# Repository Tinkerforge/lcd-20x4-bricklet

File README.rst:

LCD 20x4 Bricklet
=================

This repository contains the firmware source code and the hardware design
files. The documentation generator configs can be found at
https://github.com/Tinkerforge/generators

Repository Content
------------------

software/:
 * examples/: Examples for all supported languages
 * build/: Compiled files
 * src/: Source code of firmware
 * Makefile: Makefile to build project

hardware/:
 * Contains KiCad project files and additionally schematics as PDF

datasheets/:
 * Contains datasheets for sensors and complex ICs that are used

Hardware
--------

The hardware is designed with the open source EDA Suite KiCad
(http://www.kicad.org). Before you are able to open the files,
you have to install the Tinkerforge kicad-libraries
(https://github.com/Tinkerforge/kicad-libraries). You can either clone
them directly in hardware/ or clone them in a separate folder and
symlink them into hardware/
(ln -s kicad_path/kicad-libraries project_path/hardware). After that you
can open the .pro file in hardware/ with KiCad and from there view and
modify the schematics and the PCB layout.

Software
--------

If you want to do your own Brick/Bricklet firmware development we highly
recommend that you use our build environment setup script and read the
tutorial (https://www.tinkerforge.com/en/doc/Tutorials/Tutorial_Build_Environment/Tutorial.html).

To compile the C code we recommend you to install the newest GNU Arm Embedded
Toolchain (https://launchpad.net/gcc-arm-embedded/+download).
You also need to install bricklib (https://github.com/Tinkerforge/bricklib)
and brickletlib (https://github.com/Tinkerforge/brickletlib).

You can either clone it directly in software/src/ or clone it in a
separate folder and symlink it into software/src/
(ln -s bricklib_path/bricklib project_path/software/src/ and
ln -s brickletlib_path/brickletlib project_path/software/src/).
Finally make sure to have CMake installed
(http://www.cmake.org/cmake/resources/software.html).

After that you can build the firmware by invoking make in software/.
The firmware (.bin) can then be found in software/build/ and uploaded
with brickv (click button "Flashing" on start screen).

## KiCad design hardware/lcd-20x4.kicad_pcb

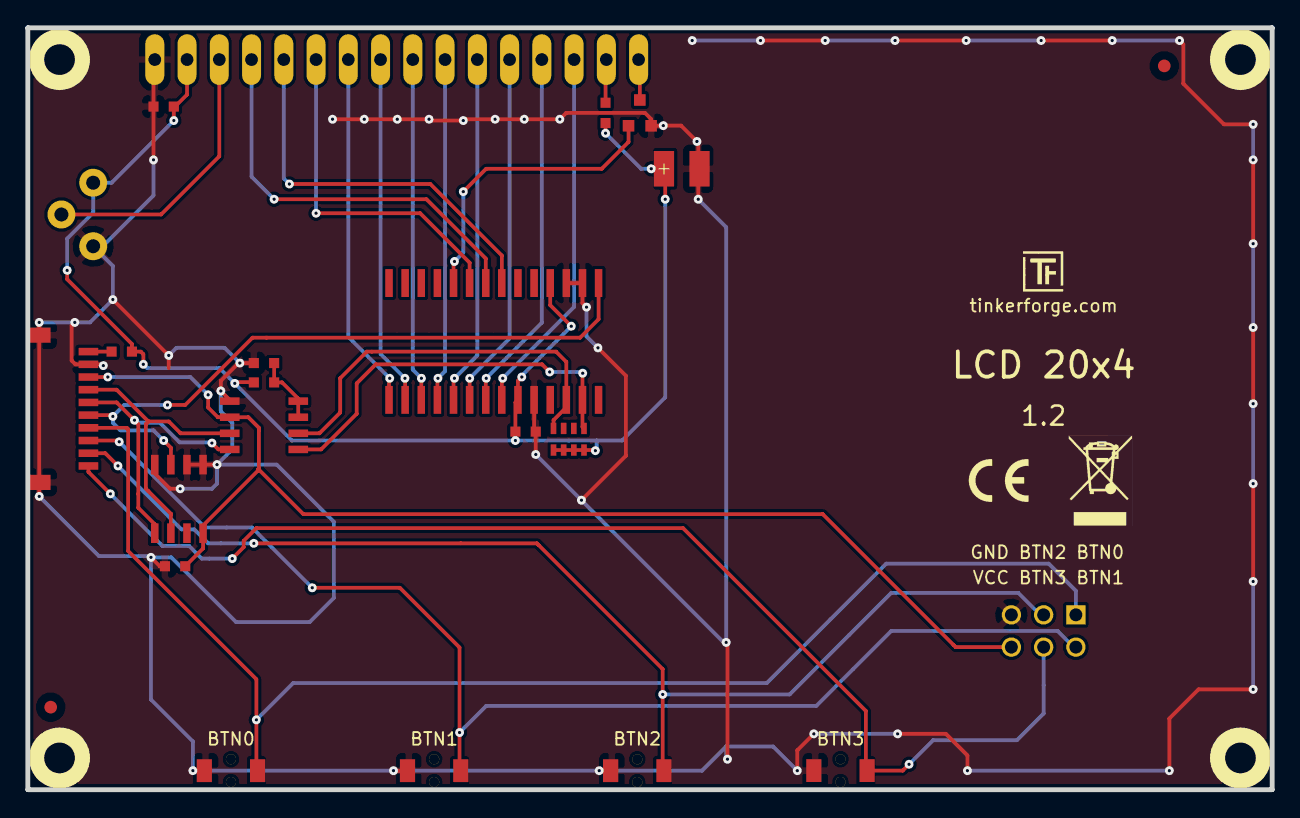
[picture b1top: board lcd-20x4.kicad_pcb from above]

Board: 2 copper layers, 98.0 x 60.0 mm, 30 parts (0 on the bottom side), 29 nets.

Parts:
C1, C2, C3, C5: 100nF; C0603
C4: 100µF/6.3V; 3528-21
FB1: FB; C0603
Fiducial_Mark: VAL**; Fiducial_Mark
Fiducial_Mark#2: VAL**; Fiducial_Mark
P1: CON-SENSOR
P2: BTN-HEADER; pin_array_3x2
Q1: 2N7002; SOT23GDS
R1: 200k; R0603
R2: 10; R0603
RP1: 4.7k; 0603X4
RV1: 10k; POT_36W
Ref**: Val**; Logo_31x31
SW1, SW2, SW3, SW4: SW_PUSH; TACT-SWITCH
U1: M24C64; SOIC8
U2: MCP23017; SOIC28
U3: PCA9306D; SOIC8
U4: LCD-20X4; LCD-20x4
U5, U6, U7, U8: DRILL; DRILL_NP
VAL: WEEE_7mm_back
VAL#2: CE_5mm

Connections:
+5V: C2.1, C4.1, C5.2, FB1.2, R1.1, R2.2, RP1.1, RP1.2, RP1.3, RP1.4, RV1.1, U2.9, U2.18, U4.2
BTN1: P1.7, P2.1, SW1.1
BTN2: P1.8, P2.2, SW2.1
BTN3: P1.9, P2.3, SW3.1
BTN4: P1.10, P2.4, SW4.1
DB0: U2.1, U4.7
DB1: U2.2, U4.8
DB2: U2.3, U4.9
DB3: U2.4, U4.10
DB4: U2.5, U4.11
DB5: U2.6, U4.12
DB6: U2.7, U4.13
DB7: U2.8, U4.14
EN: U2.23, U4.6
GND: C1.1, C2.2, C3.2, C4.2, C5.1, P1.2, P1.EP, P2.5, Q1.S, RV1.3, SW1.2, SW2.2, SW3.2, SW4.2, U1.1, U1.2, U1.4, U2.10, U2.16, U2.17, U3.1, U4.1
unnamed: C3.1, R1.2, U3.7, U3.8
unnamed: FB1.1, P1.1
unnamed: Q1.D, U4.16
unnamed: R2.1, U4.15
unnamed: RV1.2, U4.3
RS: U2.22, U4.4
RW: U2.21, U4.5
SCL: P1.4, U1.6, U3.3
SCL2: RP1.8, U2.12, U3.6
SDA: P1.5, U1.5, U3.4
SDA2: RP1.5, U2.13, U3.5
SEL: P1.6, U1.3, U2.15
SW-BACK: Q1.G, U2.24
VCC: C1.2, P1.3, P2.6, U1.8, U3.2

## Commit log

2011-08-25 initial hardware source commit
2011-08-25 add project description
2011-09-13 add java bindings and examples
2011-09-14 limit line length of java examples to 100 characters
2011-09-23 Add C# examples and bindings
2011-10-05 Remove Bindings and IP Connection (these are generated and they change too often) and rename bindings to examples
2011-10-05 add tinkerforge package to python imports
2011-10-06 remove faulty gcc commandline invocation
2011-10-06 add firmware version and name
2011-11-20 use clear display wait time, we experienced problems without it
2012-02-14 add compatability for different tick types
2012-02-15 Add changelog
2012-02-15 Move software changelog to software folder
2012-04-25 Unify capitalization of "IP connection" in examples
2012-05-09 Add PHP examples
2012-05-13 Add standard LCD charset PDF
2012-05-14 java: Remove unnecessary new String(...) calls
2012-05-21 Add Unicode examples
2012-05-21 Shorten some long lines in Unicode examples
2012-05-25 Add Ruby examples
2012-06-05 Fix register_callback syntax error in Ruby examples on Windows
2012-06-12 Use correct term 'Bricklet' in example code error message
2012-06-12 Prefer IPConnection destroy over join_thread
2012-07-01 Add generate_makefile.bat for windows
2012-07-25 Add Delphi examples
2012-08-08 delphi: Add comment about UID
2012-09-03 version v1.2 of lcd * add 4th button * add 2x3 pin header * connect reset pin of mcp23017 to vcc
2012-09-06 change mounting hole soldermask: add soldermask bottom
2012-09-07 Ignore temporary build files
2012-09-26 examples: Map ÄÖÜ to äöü of LCD charset
2012-10-04 Extend .gitignore
2012-10-24 Make cmake find the correct objcopy binary
    On some systems cmake uses the wrong objcopy binary, tell it to use
    the correct one.
2012-11-13 Support for protocol 2.0
2012-11-29 Make examples compatible to Protocol V2.0
2012-11-29 Make Ruby examples Protocol 2.0 compatible
2012-11-29 Make C examples Protocol 2.0 compatible
2012-11-29 Make PHP examples Protocol 2.0 compatible
2012-11-30 Make delphi examples compatible to protocol 2.0
2012-11-30 Fix invalid parameter checks
2012-11-30 delphi: Remove unnecessary parentheses and call destructor again
2012-12-05 Add protocol 2.0 compatability to C# bindings
2012-12-05 Add compatability for LCD20x4 Bricklet V1.2
2012-12-05 Remove unnecessary configuration
2012-12-05 Fix typo (wrong button number)
2012-12-05 Configure to default before pullup (seems to be a silicon bug?)
2012-12-05 Add support for LCD 20x4 Bricklet V1.2 to v1.x.y branch
2012-12-06 Fix C example
2012-12-11 Avoid g++ warnings about missing casts in C examples
2012-12-13 fix lcd schematic
2013-01-09 Use specific device object for callbacks
2013-01-14 Add Unicode example for Delphi
2013-01-15 Return setter if return expected in write_line
2013-01-17 Make Java examples compatible to new listener approach
2013-01-21 Fix Python example
2013-01-21 Use common text for Ruby Unicode example
2013-01-25 Add support for custom characters
2013-02-07 Use IPconnection disconnect explicitly in examples
2013-02-14 Fix comments in Unicode examples
2013-02-18 Add Visual Basic .NET examples
2013-03-26 Add default text functionality
2013-04-02 Save some bytes to make firmware small enough for EEPROM if O1 is used
2013-04-23 Fix cursor position logic
    At end of line and related to the custom character API.
    Calculate cursor position for next line at end of line and keep track of
    current cursor position to restore it after custom character get/set.
2013-05-06 Fix HW version detection if Servo Brick port a is used
2013-05-06 Add accidentially removed default_text_counter again (thanks to Jan Sandbrink) and save some more bytes
2013-05-22 Add missing return statements in error paths
2013-06-03 Split Firmware in HW Version 1.1 and 1.2
2013-08-13 Add shell examples
2013-08-21 windows: Don't trigger a build in generate_makefile.bat
    Also use normal make instead of a special named one.
2014-01-10 Add Perl examples
2014-01-14 perl: Fix subroutine signature
2014-01-15 php: Use const for constant values
2014-02-07 Add Mathematica examples
2014-02-07 mathematica: Disable incomplete Unicode examples
2014-02-10 perl: fixed namespace
2014-02-11 javascript: adding examples
2014-02-11 javascript: short examples
2014-02-18 javascript: examples fixed
2014-02-20 javascript: adding html examples
2014-02-24 javascript: port 4280, startExample()
2014-02-28 javascript: Break long lines and cleanup whitespace
2014-03-05 Add LabVIEW examples
2014-03-06 labview: Add examples in LV2010 format
2014-03-25 matlab: add examples
2014-03-28 perl: Fix warnings
2014-04-02 java: Unify constants style
2014-04-02 perl: Unify print style
2014-04-17 matlab: Adapt examples to new callback style
2014-04-17 matlab: Add parentheses to make pygments happy
2014-07-15 java: Replace System.console() usage with an Eclipse compatible pattern
2014-12-02 Use ReadLine instead of ReadKey for C# example
2015-02-13 vbnet: Use ReadLine instead of ReadKey
    Because ReadKey doesn't work with a pipe as stdin on the RED Brick.
2015-03-02 windows: Stop cmake from searching for mingw32-make.exe
    Using MinGW Makefiles as generator makes cmake search for mingw32-make.exe
    which might not be installed because GnuWin32's make.exe is used instead.
2015-03-26 update to latest version
2015-04-09 c: Whitespace
2015-06-19 Fix typo
2015-06-24 javascript: Clean up output creation
2015-06-29 octave: Handle short difference between Octave 3.6 and 3.8
    In Octave 3.6 a short is not automatically handled as a number.
2015-07-22 Unify name of callback example
2015-07-25 Make JavaScript browser example textarea readonly
2015-07-27 Cleanup C/C++, C#, Java, Python and Ruby examples
2015-07-27 Simplify variable names in examples again
2015-07-29 Reformat changelog
2015-08-07 Use full device class name in Python examples
2015-08-12 Fix minor warnings in C/C++ examples
2015-08-14 Cleanup Delphi examples
2015-08-18 Cleanup VB.NET examples
2015-08-19 Cleanup Perl examples
2015-08-20 Fix typo in C/C++ example
2015-09-09 shell: Use printf instead of echo -e
    Because echo -e doesn't work with dash.
2015-09-09 Duplicate cmake call to fix bug during cmake creation
2015-09-11 javascript: Fix example name
2015-10-01 Generator based example cleanup
2015-11-12 matlab: Fix callback handling for R2014a
    http://undocumentedmatlab.com/blog/matlab-callbacks-for-java-events-in-r2014a
2015-11-25 Include date and commit into changelog
2016-05-18 c: Add missing device destroy call
2016-06-17 fix weee logo
2016-07-01 Make the change UID comment more explicit
2017-04-13 csharp: Adapt example
2017-05-12 python: Use isinstance instead of type
2017-06-02 octave: Use javaObject instead of deprecated java_new
2017-11-02 add missing pcb
2017-11-02 Add 3d information (final)
2017-11-02 Add 3d model (*.step & *.FCStd)
2017-11-30 Update examples from generator
2017-12-07 mathematica: Also generate .nb files
2018-01-26 c: Fine-tune printf format
2018-02-19 javascript: Close div tag correctly
2018-02-20 Cleanup KiCad libraries config
    Ensure LibDir=kicad-libraries and LibName1=tinkerforge.
    Remove special library.
2018-05-24 perl: Use strict in examples
2018-07-11 Add Makefile with docker support
2018-07-11 Remove obsolete generate_makefile scripts
2018-07-11 Update directory structure and build instructions
2018-11-06 Add rust examples
2018-11-07 rust: Accept host names for ip connection, fix naming inconsistencies
2018-11-07 rust: Rename callback receivers.
2018-11-08 rust: Fixed string handling.
2018-12-14 Add go examples.
2018-12-18 go: Change import path.
2018-12-18 go: Change import path again.
2018-12-20 rust: Reformat examples.
2019-01-24 mqtt: Add examples.
2019-01-24 mqtt: Fix example header.
2019-01-24 mqtt: Remove executable bit in example permissions.
2019-01-24 go: Minor example fixes.
2019-01-24 mqtt: Minor example fixes.
2019-08-13 Document font in common style
2019-08-22 c: Adapt to bindings changes
2020-01-13 examples: Use python3 input instead of python2 raw_input.
2020-01-13 examples: mqtt: Remove trailing whitespace.
2020-01-14 examples: Use python3 input by default.
2020-03-16 rust: Update to new skeleton
2020-03-16 Whitespace
2020-04-07 examples: rust: Always block when calling bindings functions.
2021-01-15 rust: Fix compiler warnings
2021-01-15 python: Disable pylint warnings
2021-10-25 Update KiCad link
    https://www.kicad.org/blog/2021/10/Avoid-links-to-former-kicad-domain/
2022-07-06 Add license files.

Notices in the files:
hardware/lcd-20x4.kicad_pcb:
Licensed under CERN OHL v.1.1
Copyright (©) 2011, B.Nordmeyer
Copyright Tinkerforge GmbH 2011.
This documentation describes Open Hardware and is licensed under the
CERN OHL v. 1.1.
